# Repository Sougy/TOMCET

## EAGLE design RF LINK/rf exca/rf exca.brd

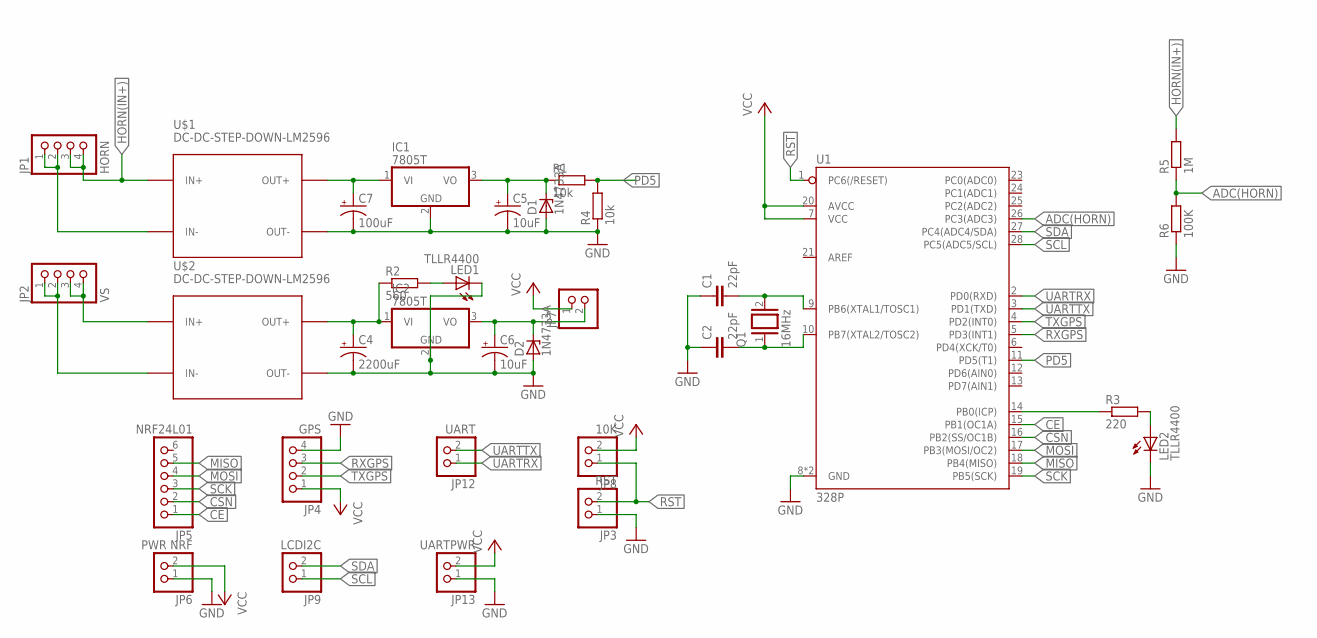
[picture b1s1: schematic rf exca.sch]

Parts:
C1, C2: 22pF; C025-024X044
C4: 2200uF; E5-13
C5, C6: 10uF; E2,5-6E
C7: 100uF; E2,5-7
D1, D2: 1N4733A; DO41Z10
IC1, IC2: 7805T; TO220H
JP1: HORN; 1X04
JP2: VS; 1X04
JP3: RST; 1X02
JP4: GPS; 1X04
JP5: NRF24L01; 1X06
JP6: PWR NRF; 1X02
JP7: PINHD-1X2; 1X02
JP8: 10K; 1X02
JP9: LCDI2C; 1X02
JP12: UART; 1X02
JP13: UARTPWR; 1X02
LED1, LED2: TLLR4400; LED3MM
Q1: 16MHz; QS
R1, R4: 10k; 0207/12
R2: 560; 0207/12
R3: 220; 0207/12
R5: 1M; 0207/12
R6: 100K; 0207/12
U1: 328P; DIP28
U$1, U$2: DC-DC-STEP-DOWN-LM2596

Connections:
ADC(HORN): R5.1, R6.2, U1.26 (PC3(ADC3))
CE: JP5.1, U1.15 (PB1(OC1A))
CSN: JP5.2, U1.16 (PB2(SS/OC1B))
GND: C1.1, C2.1, C4.-, C5.-, C6.-, C7.-, D1.A, D2.A, IC1.2 (GND), IC2.2 (GND), JP3.1, JP4.4, JP6.1, JP13.1, LED1.K (C), LED2.K (C), R4.1, R6.1, U1.8 (GND), U1.22 (GND), U$1.OUT-, U$2.OUT-
HORN(IN+): JP1.3, JP1.4, R5.2, U$1.IN+
MISO: JP5.5, U1.18 (PB4(MISO))
MOSI: JP5.4, U1.17 (PB3(MOSI/OC2))
unnamed: C1.2, Q1.2, U1.9 (PB6(XTAL1/TOSC1))
unnamed: C2.2, Q1.1, U1.10 (PB7(XTAL2/TOSC2))
unnamed: JP1.1, JP1.2, U$1.IN-
unnamed: JP2.3, JP2.4, U$2.IN+
unnamed: JP2.1, JP2.2, U$2.IN-
unnamed: LED2.A, R3.2
unnamed: LED1.A, R2.2
unnamed: C7.+, IC1.1 (VI), U$1.OUT+
unnamed: C6.+, D2.C, IC2.3 (VO), JP7.2
unnamed: C5.+, D1.C, IC1.3 (VO), R1.1
unnamed: R3.1, U1.14 (PB0(ICP))
unnamed: C4.+, IC2.1 (VI), R2.1, U$2.OUT+
PD5: R1.2, R4.2, U1.11 (PD5(T1))
RST: JP3.2, JP8.1, U1.1 (PC6(/RESET))
RXGPS: JP4.3, U1.5 (PD3(INT1))
SCK: JP5.3, U1.19 (PB5(SCK))
SCL: JP9.1, U1.28 (PC5(ADC5/SCL))
SDA: JP9.2, U1.27 (PC4(ADC4/SDA))
TXGPS: JP4.2, U1.4 (PD2(INT0))
UARTRX: JP12.1, U1.2 (PD0(RXD))
UARTTX: JP12.2, U1.3 (PD1(TXD))
VCC: JP4.1, JP6.2, JP7.1, JP8.2, JP13.2, U1.7 (VCC), U1.20 (AVCC)

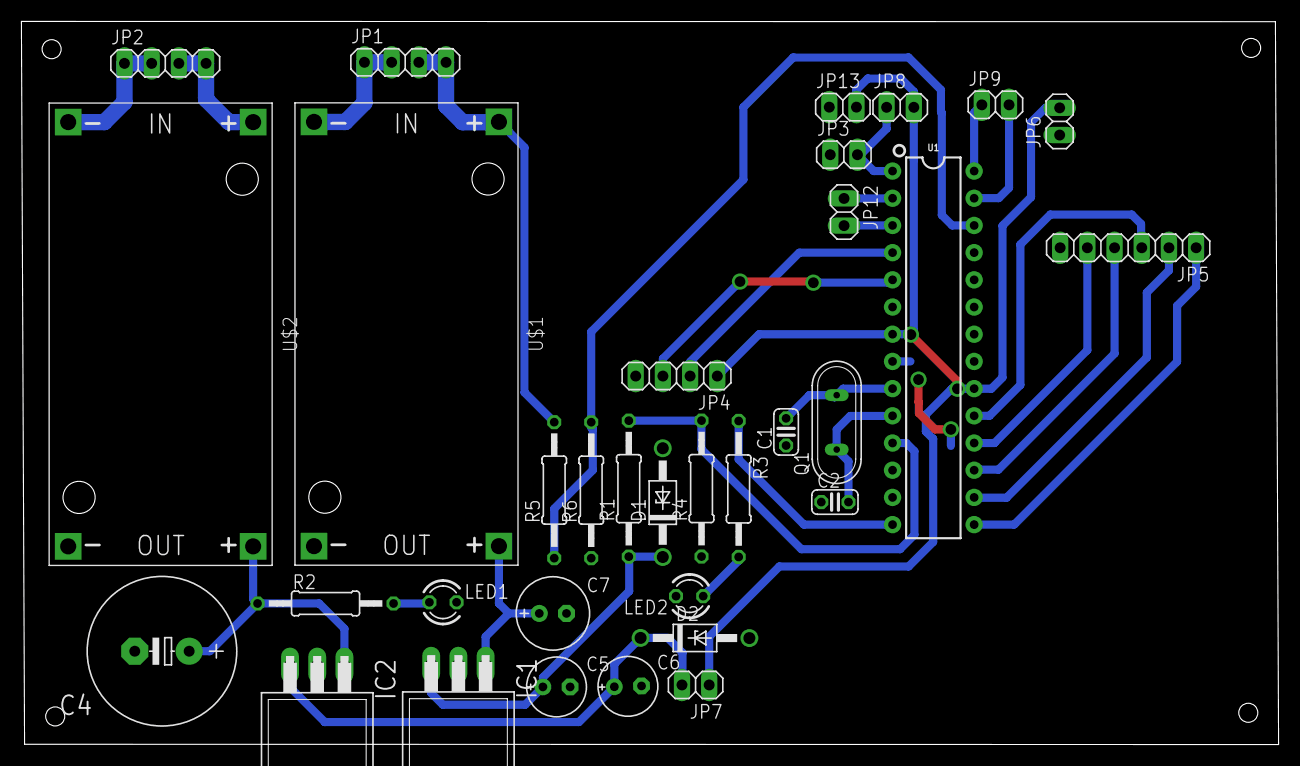
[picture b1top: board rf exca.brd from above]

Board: 2 copper layers, 117.4 x 67.5 mm, 33 parts (0 on the bottom side), 29 nets.

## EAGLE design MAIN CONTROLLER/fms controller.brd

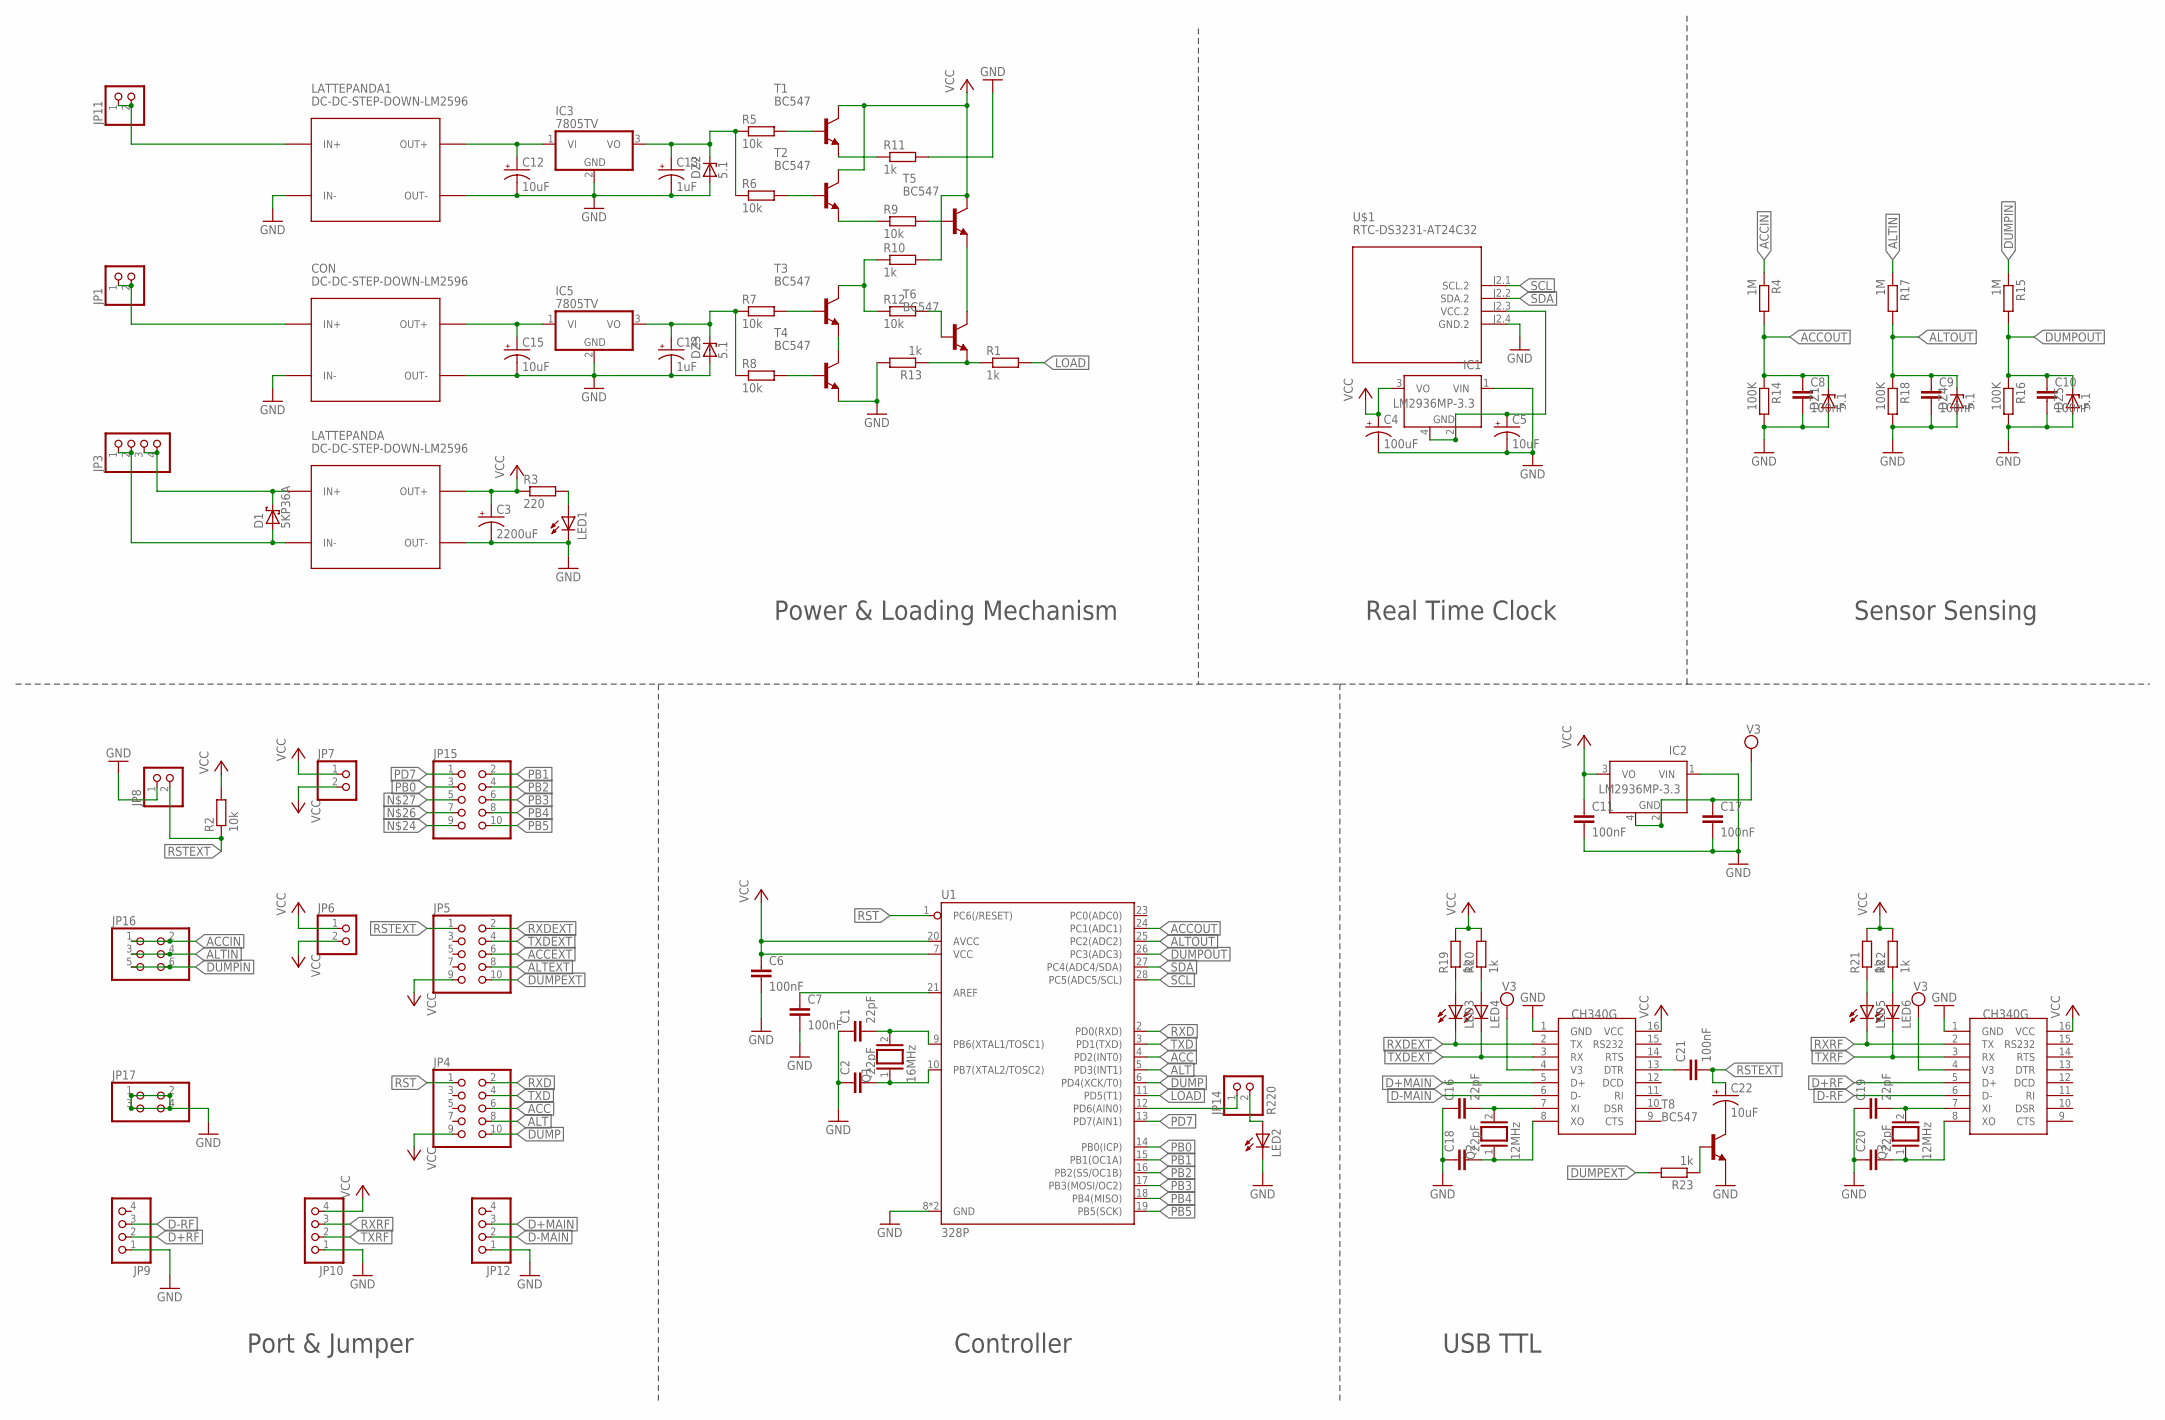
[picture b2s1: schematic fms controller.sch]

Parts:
C1, C2, C16, C18, C19, C20: 22pF; C2.5-3
C3: 2200uF; E5-13
C4: 100uF; E2-5
C5, C12, C15, C22: 10uF; E2-5
C6, C7, C8, C9, C10, C11, C17, C21: 100nF; C025-040X050
C13, C14: 1uF; E2-5
CON: DC-DC-STEP-DOWN-LM2596
D1: 5KP36A; P6T15
DZ1, DZ2, DZ3, DZ4, DZ5: 5.1; DO35Z10
IC1, IC2: LM2936MP-3.3; SOT223
IC3, IC5: 7805TV; TO220V
JP1, JP6, JP7, JP8, JP11: PINHD-1X2; 1X02
JP3, JP9, JP10, JP12: PINHD-1X4; 1X04
JP4, JP5, JP15: PINHD-2X5; 2X05
JP14: R220; 1X02
JP16: PINHD-2X3; 2X03
JP17: PINHD-2X2; 2X02
LATTEPANDA, LATTEPANDA1: DC-DC-STEP-DOWN-LM2596
LED1, LED2, LED3, LED4, LED5, LED6: LED3MM
Q1: 16MHz; QS
Q2, Q3: 12MHz; QS
R1, R10, R11, R13, R19, R20, R21, R22, R23: 1k; 0309/10
R2, R5, R6, R7, R8, R9, R12: 10k; 0309/10
R3: 220; 0309/10
R4, R15, R17: 1M; 0309/10
R14, R16, R18: 100K; 0309/10
T1, T2, T3, T4, T5, T6, T8: BC547; TO92
U1: 328P; DIP28
U$1: RTC-DS3231-AT24C32
U$2, U$3: CH340G; SOIC16

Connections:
ACC: JP4.6, U1.4 (PD2(INT0))
ACCEXT: JP5.6
ACCIN: JP16.1, JP16.2, R4.1
ACCOUT: C8.1, DZ1.C, R4.2, R14.1, U1.24 (PC1(ADC1))
ALT: JP4.8, U1.5 (PD3(INT1))
ALTEXT: JP5.8
ALTIN: JP16.3, JP16.4, R17.1
ALTOUT: C9.1, DZ4.C, R17.2, R18.1, U1.25 (PC2(ADC2))
D+MAIN: JP12.3, U$2.5 (D+)
D+RF: JP9.2, U$3.5 (D+)
D-MAIN: JP12.2, U$2.6 (D-)
D-RF: JP9.3, U$3.6 (D-)
DUMP: JP4.10, U1.6 (PD4(XCK/T0))
DUMPEXT: JP5.10, R23.2
DUMPIN: JP16.5, JP16.6, R15.1
DUMPOUT: C10.1, DZ5.C, R15.2, R16.1, U1.26 (PC3(ADC3))
GND: C1.1, C2.1, C3.-, C4.-, C5.-, C6.2, C7.2, C8.2, C9.2, C10.2, C11.2, C12.-, C13.-, C14.-, C15.-, C16.1, C17.2, C18.1, C19.1, C20.1, CON.IN-, CON.OUT-, DZ1.A, DZ2.A, DZ3.A, DZ4.A, DZ5.A, IC1.1 (VIN), IC2.1 (VIN), IC3.2 (GND), IC5.2 (GND), JP8.1, JP9.1, JP10.1, JP12.1, JP17.1, JP17.2, JP17.3, JP17.4, LATTEPANDA.OUT-, LATTEPANDA1.IN-, LATTEPANDA1.OUT-, LED1.K (C), LED2.K (C), R11.2, R13.2, R14.2, R16.2, R18.2, T4.1 (E), T8.1 (E), U1.8 (GND), U1.22 (GND), U$1.J2.4 (GND.2), U$2.1 (GND), U$3.1 (GND)
LOAD: R1.2, U1.11 (PD5(T1))
unnamed: JP11.1, JP11.2, LATTEPANDA1.IN+
unnamed: CON.IN+, JP1.1, JP1.2
unnamed: LED1.A, R3.2
unnamed: D1.A, JP3.1, JP3.2, LATTEPANDA.IN-
unnamed: D1.C, JP3.3, JP3.4, LATTEPANDA.IN+
unnamed: C12.+, IC3.1 (VI), LATTEPANDA1.OUT+
unnamed: C1.2, Q1.2, U1.9 (PB6(XTAL1/TOSC1))
unnamed: JP14.1, U1.12 (PD6(AIN0))
unnamed: C13.+, DZ2.C, IC3.3 (VO), R5.1, R6.1
unnamed: R1.1, R13.1, T6.1 (E)
unnamed: C15.+, CON.OUT+, IC5.1 (VI)
unnamed: C2.2, Q1.1, U1.10 (PB7(XTAL2/TOSC2))
unnamed: C14.+, DZ3.C, IC5.3 (VO), R7.1, R8.1
unnamed: JP14.2, LED2.A
unnamed: C5.+, IC1.2 (GND), IC1.4 (GND), U$1.J2.3 (VCC.2)
unnamed: C7.1, U1.21 (AREF)
unnamed: C19.2, Q3.2, U$3.7 (XI)
unnamed: R11.1, T1.1 (E)
unnamed: C20.2, Q3.1, U$3.8 (XO)
unnamed: C16.2, Q2.2, U$2.7 (XI)
unnamed: R5.2, T1.2 (B)
unnamed: C18.2, Q2.1, U$2.8 (XO)
unnamed: R10.1, R12.1, T3.3 (C)
unnamed: R6.2, T2.2 (B)
unnamed: C21.1, U$2.13 (DTR)
unnamed: R7.2, T3.2 (B)
unnamed: C22.-, T8.3 (C)
unnamed: R9.1, T2.1 (E)
unnamed: R9.2, T5.2 (B)
unnamed: R8.2, T4.2 (B)
unnamed: LED4.A, R20.1
unnamed: T3.1 (E), T4.3 (C)
unnamed: LED3.A, R19.1
unnamed: R12.2, T6.2 (B)
unnamed: T5.1 (E), T6.3 (C)
unnamed: LED5.A, R21.1
unnamed: LED6.A, R22.1
unnamed: R23.1, T8.2 (B)
PB0: JP15.3, U1.14 (PB0(ICP))
PB1: JP15.2, U1.15 (PB1(OC1A))
PB2: JP15.4, U1.16 (PB2(SS/OC1B))
PB3: JP15.6, U1.17 (PB3(MOSI/OC2))
PB4: JP15.8, U1.18 (PB4(MISO))
PB5: JP15.10, U1.19 (PB5(SCK))
PD7: JP15.1, U1.13 (PD7(AIN1))
RST: JP4.1, U1.1 (PC6(/RESET))
RSTEXT: C21.2, C22.+, JP5.1, JP8.2, R2.1
RXD: JP4.2, U1.2 (PD0(RXD))
RXDEXT: JP5.2, LED3.K (C), U$2.2 (TX)
RXRF: JP10.3, LED5.K (C), U$3.2 (TX)
SCL: U1.28 (PC5(ADC5/SCL)), U$1.J2.1 (SCL.2)
SDA: U1.27 (PC4(ADC4/SDA)), U$1.J2.2 (SDA.2)
TXD: JP4.4, U1.3 (PD1(TXD))
TXDEXT: JP5.4, LED4.K (C), U$2.3 (RX)
TXRF: JP10.2, LED6.K (C), U$3.3 (RX)
VCC: C3.+, C4.+, C6.1, C11.1, IC1.3 (VO), IC2.3 (VO), JP4.9, JP5.9, JP6.1, JP6.2, JP7.1, JP7.2, JP10.4, LATTEPANDA.OUT+, R2.2, R3.1, R10.2, R19.2, R20.2, R21.2, R22.2, T1.3 (C), T2.3 (C), T5.3 (C), U1.7 (VCC), U1.20 (AVCC), U$2.16 (VCC), U$3.16 (VCC)
VSS: C17.1, IC2.2 (GND), IC2.4 (GND), U$2.4 (V3), U$3.4 (V3)

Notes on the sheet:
Power & Loading Mechanism
Real Time Clock
Sensor Sensing
Port & Jumper
Controller
USB TTL

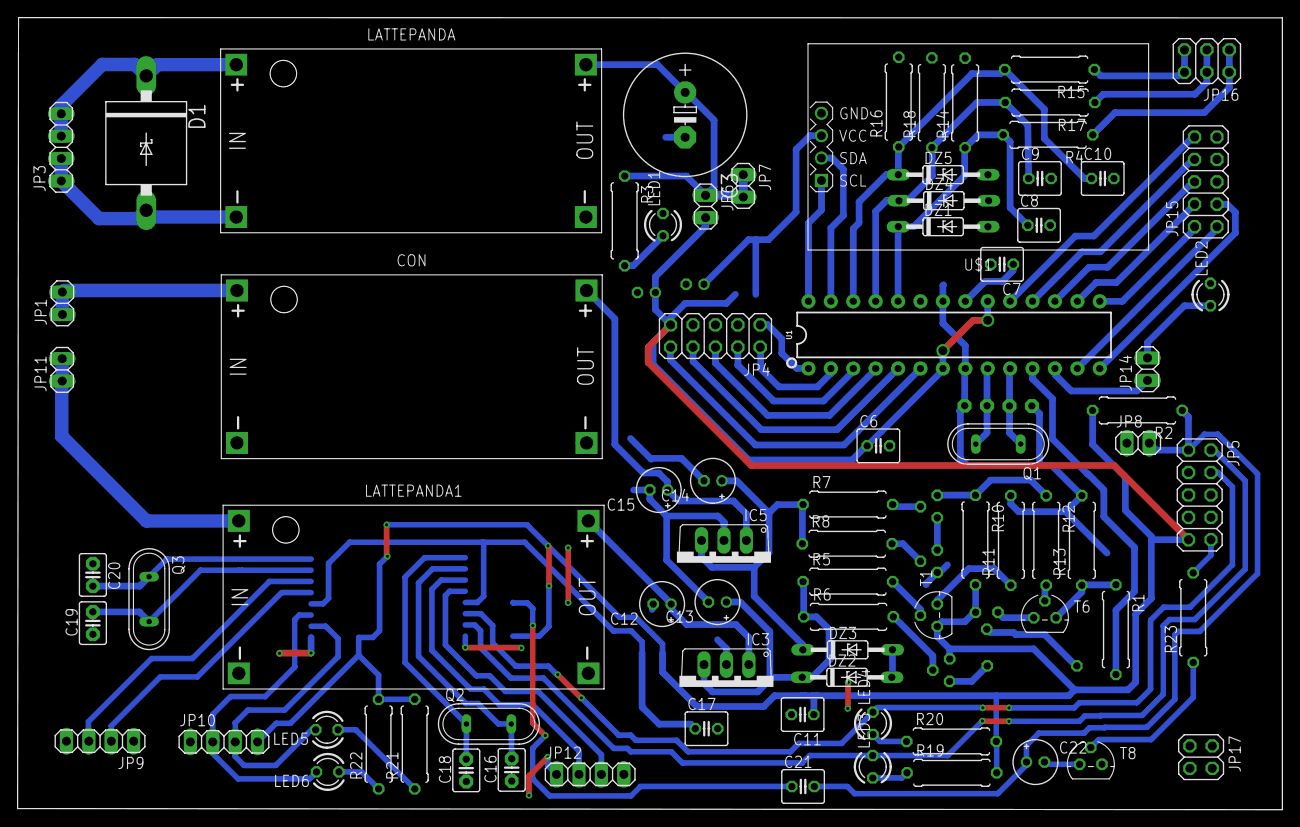
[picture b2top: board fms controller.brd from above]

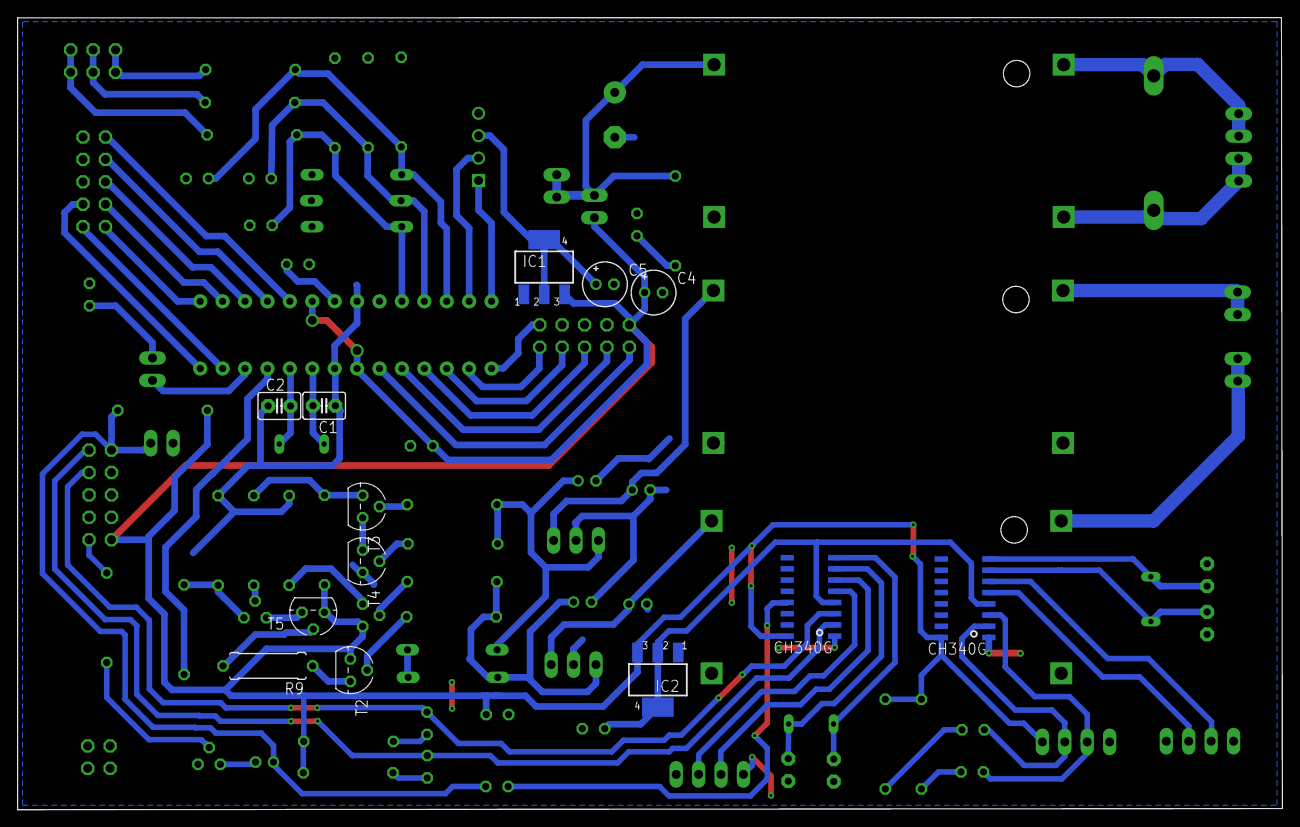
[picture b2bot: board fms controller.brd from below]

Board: 2 copper layers, 143.3 x 89.8 mm, 93 parts (13 on the bottom side), 73 nets.

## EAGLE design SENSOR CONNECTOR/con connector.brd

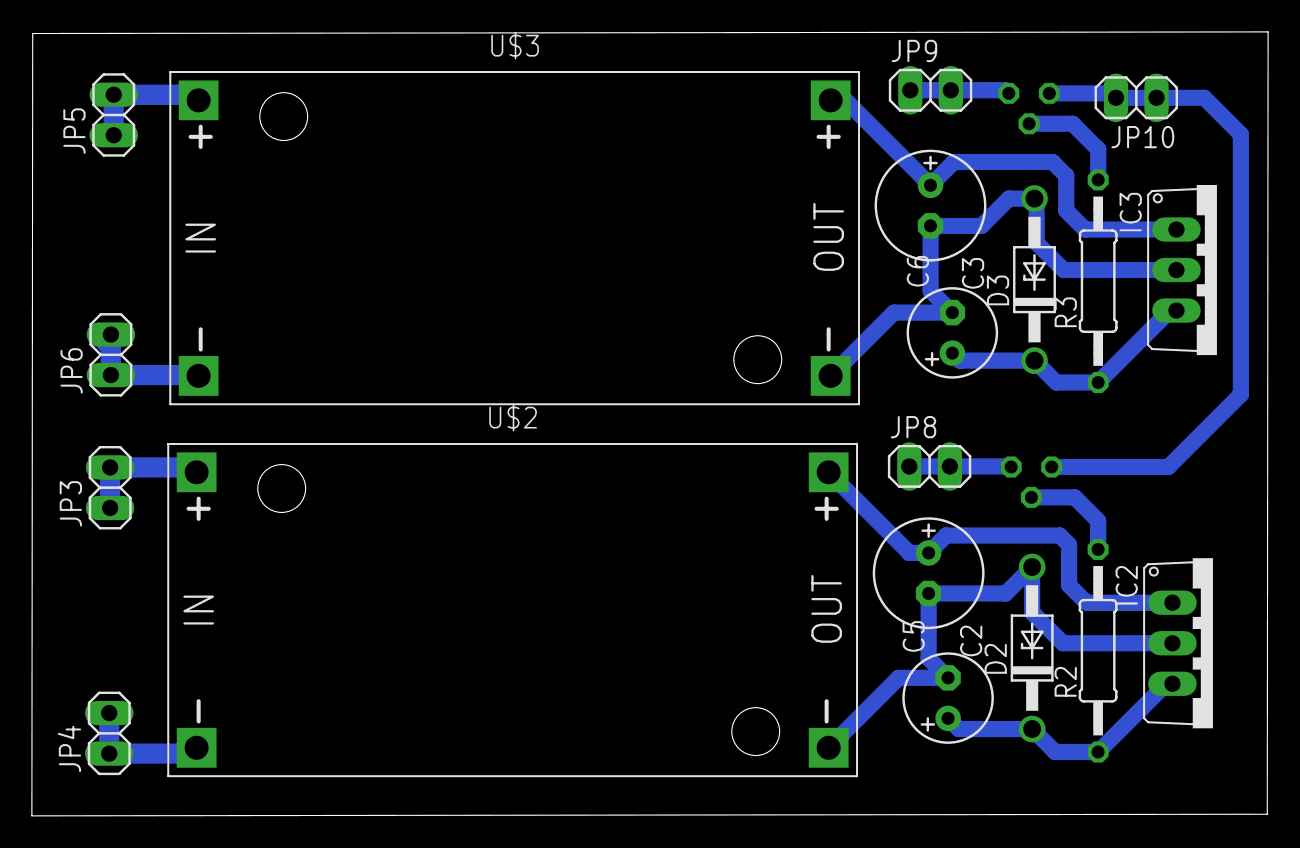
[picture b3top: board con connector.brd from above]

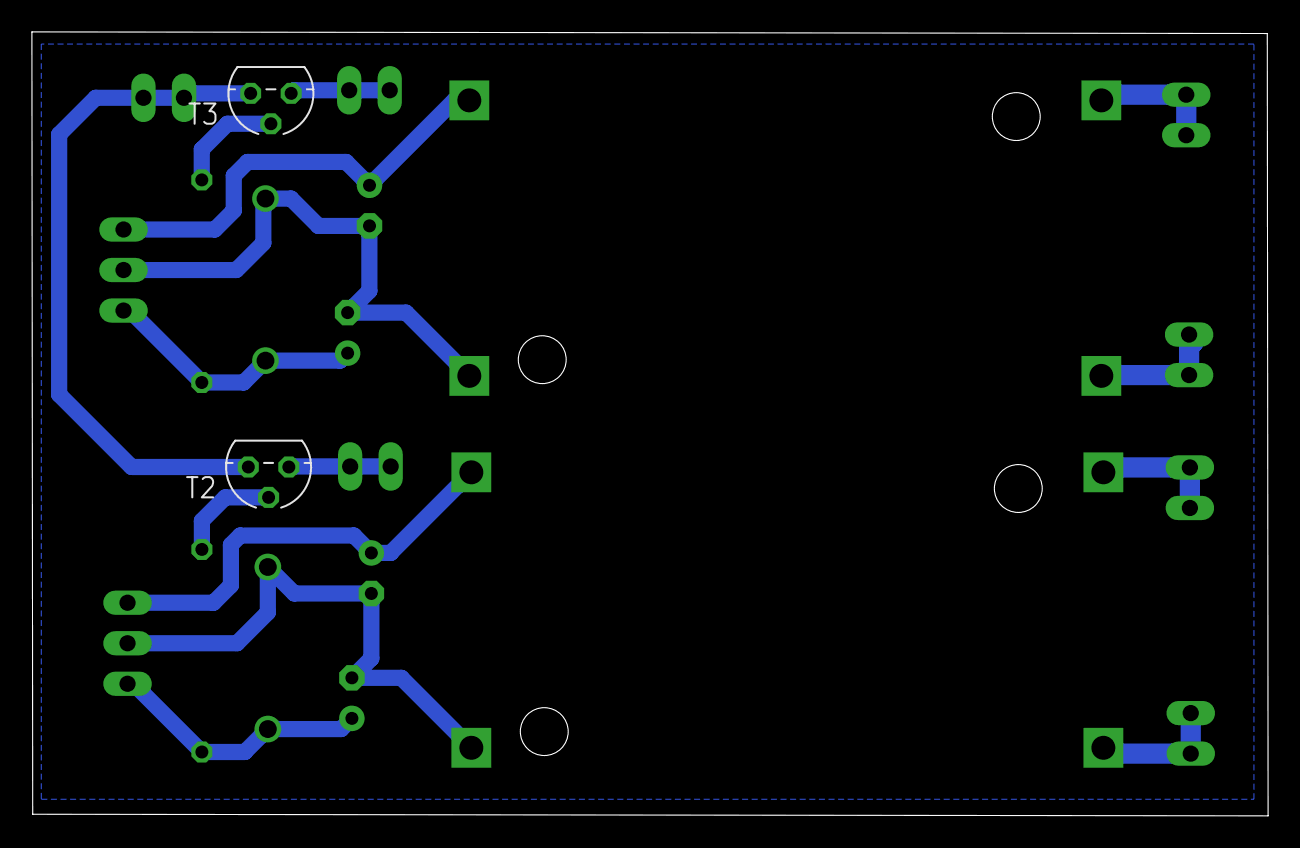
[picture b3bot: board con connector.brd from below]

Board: 2 copper layers, 77.5 x 49.1 mm, 21 parts (2 on the bottom side), 14 nets.

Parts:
C2: 100uF; E2,5-7
C3: 100uF'; E2,5-7
C5, C6: 10uF; E2,5-6
D2, D3: 1N4733A; DO41Z10
IC2, IC3: 7805TV; TO220V
JP3, JP4, JP5, JP6, JP8, JP9: 1X02
JP10: GND; 1X02
R2, R3: 10k; 0207/12
T2, T3: BC547; TO92
U$2, U$3: DC-DC-STEP-DOWN-LM2596

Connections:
GND: C2.-, C3.-, C5.-, C6.-, D2.A, D3.A, IC2.2, IC3.2, U$2.OUT-, U$3.OUT-
unnamed: C2.+, IC2.1, U$2.OUT+
unnamed: C3.+, IC3.1, U$3.OUT+
unnamed: C5.+, D2.C, IC2.3, R2.1
unnamed: C6.+, D3.C, IC3.3, R3.1
unnamed: R2.2, T2.2
unnamed: R3.2, T3.2
unnamed: JP10.1, JP10.2, T2.1, T3.1
unnamed: JP3.1, JP3.2, U$2.IN+
unnamed: JP4.1, JP4.2, U$2.IN-
unnamed: JP5.1, JP5.2, U$3.IN+
unnamed: JP6.1, JP6.2, U$3.IN-
unnamed: JP8.1, JP8.2, T2.3
unnamed: JP9.1, JP9.2, T3.3

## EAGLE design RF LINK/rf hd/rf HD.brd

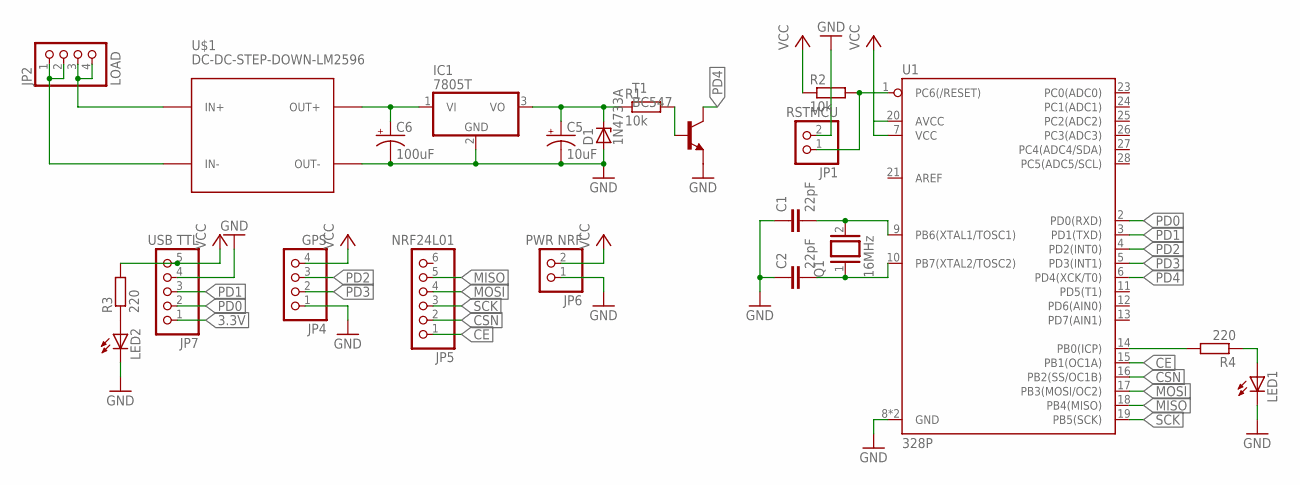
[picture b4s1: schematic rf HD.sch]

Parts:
C1, C2: 22pF; C025-024X044
C5: 10uF; E2,5-6E
C6: 100uF; E2,5-7
D1: 1N4733A; DO41Z10
IC1: 7805T; TO220H
JP1: RSTMCU; 1X02
JP2: LOAD; 1X04
JP4: GPS; 1X04
JP5: NRF24L01; 1X06
JP6: PWR NRF; 1X02
JP7: USB TTL; 1X05
LED1, LED2: LED3MM
Q1: 16MHz; QS
R1, R2: 10k; 0207/12
R3, R4: 220; 0207/12
T1: BC547; TO92
U1: 328P; DIP28
U$1: DC-DC-STEP-DOWN-LM2596

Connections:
3.3V: JP7.1
CE: JP5.1, U1.15 (PB1(OC1A))
CSN: JP5.2, U1.16 (PB2(SS/OC1B))
GND: C1.1, C2.1, C5.-, C6.-, D1.A, IC1.2 (GND), JP1.2, JP4.1, JP6.1, JP7.4, LED1.K (C), LED2.K (C), T1.1 (E), U1.8 (GND), U1.22 (GND), U$1.OUT-
MISO: JP5.5, U1.18 (PB4(MISO))
MOSI: JP5.4, U1.17 (PB3(MOSI/OC2))
unnamed: C1.2, Q1.2, U1.9 (PB6(XTAL1/TOSC1))
unnamed: C2.2, Q1.1, U1.10 (PB7(XTAL2/TOSC2))
unnamed: R1.2, T1.2 (B)
unnamed: JP1.1, R2.2, U1.1 (PC6(/RESET))
unnamed: JP2.3, JP2.4, U$1.IN+
unnamed: C5.+, D1.C, IC1.3 (VO), R1.1
unnamed: LED2.A, R3.1
unnamed: LED1.A, R4.1
unnamed: JP2.1, JP2.2, U$1.IN-
unnamed: C6.+, IC1.1 (VI), U$1.OUT+
PB0: R4.2, U1.14 (PB0(ICP))
PD0: JP7.2, U1.2 (PD0(RXD))
PD1: JP7.3, U1.3 (PD1(TXD))
PD2: JP4.3, U1.4 (PD2(INT0))
PD3: JP4.2, U1.5 (PD3(INT1))
PD4: T1.3 (C), U1.6 (PD4(XCK/T0))
SCK: JP5.3, U1.19 (PB5(SCK))
VCC: JP4.4, JP6.2, JP7.5, R2.1, R3.2, U1.7 (VCC), U1.20 (AVCC)

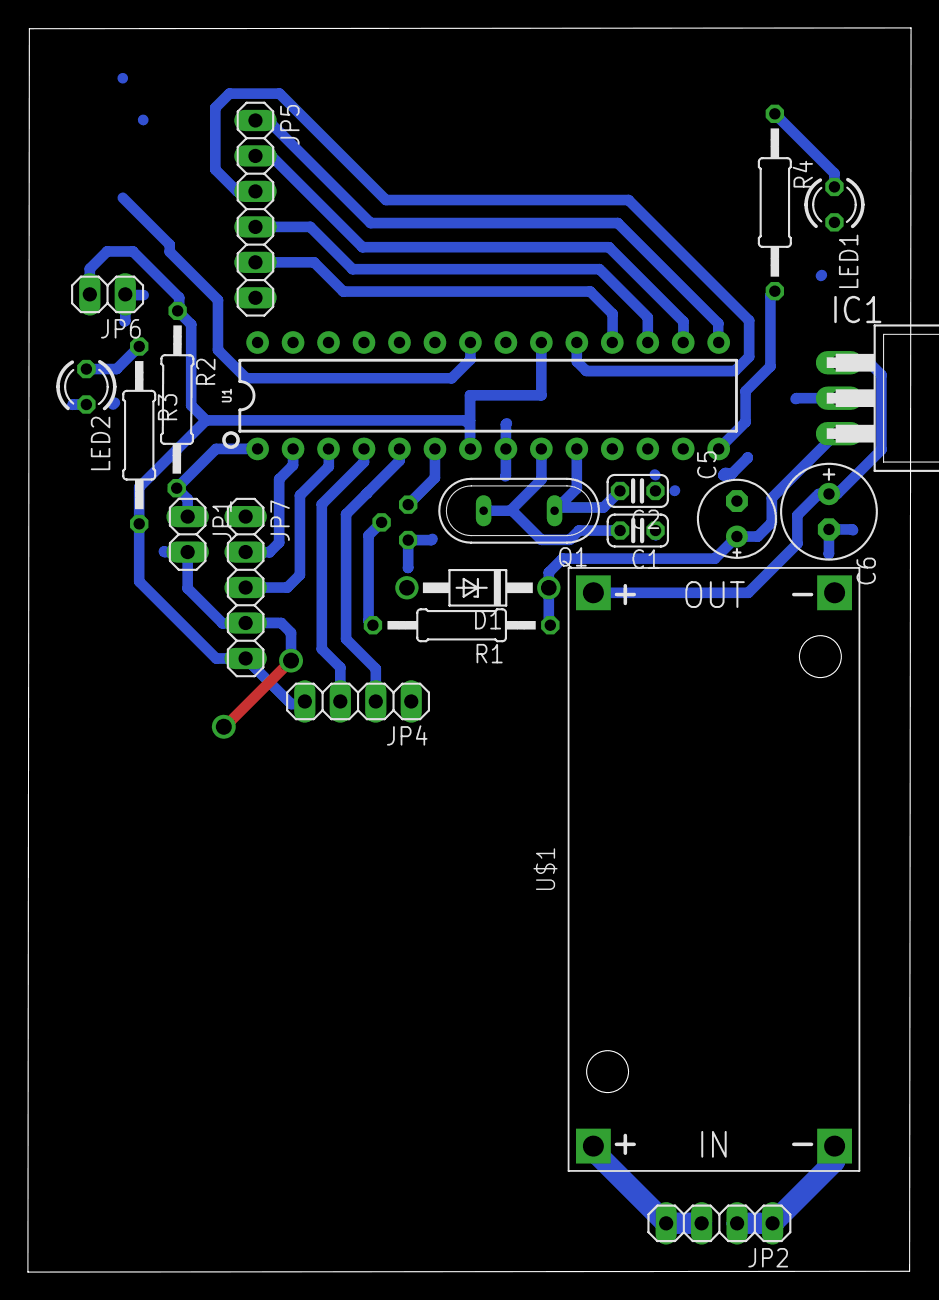
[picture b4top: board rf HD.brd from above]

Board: 2 copper layers, 63.2 x 89.1 mm, 22 parts (1 on the bottom side), 23 nets.

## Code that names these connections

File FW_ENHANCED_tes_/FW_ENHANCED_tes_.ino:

#include <Wire.h>
#include "RTClib.h"

#define HOURDIV 3600
#define MINDIV 60
#define AT24C32 0x57
//tes
DateTime now;
RTC_DS3231 rtc;

//Engine status & Sensor status
String ENGSTAT, TRIGSTAT;
unsigned long PREVSEN = 0;
unsigned long PREVSET = 0;
unsigned long PREVTES = 0;

typedef struct
{
  String DATAIN;
  String SETDATA[12];
  bool INHM   = false;
  bool START  = false;
  bool END    = false;
  uint8_t VAL = 0;
  uint8_t SEQ = 0;
  uint8_t I;
  char INBYTE;
  char MSG[20];
  byte IDX;
} SERCOM; SERCOM VARSER;

typedef struct
{
  String CURTIME;
  String CURDATE;
  uint8_t SEC;
  uint8_t MIN;
  uint8_t SEQ;
  uint32_t HR;
  char RCVDATA[12];
  char DATA2WRT[12];
  unsigned long SVDHM;
  unsigned long LASTUNIX;
  unsigned long DELTATIME;
  unsigned long ELAPSED;
  bool LTCHM = false;

} RTCOM; RTCOM VARRTC;

void setup() {
  // put your setup code here, to run once:
  DDRD &= ~(1 << PIND3); //ACC
  DDRD &= ~(1 << PIND4); //DUMP
  DDRD &= ~(1 << PIND7); //ALT
  DDRD  |= (1 << PIND6);
  PORTD |= (1 << PIND3);
  PORTD |= (1 << PIND4);
  PORTD |= (1 << PIND7);
  Wire.begin();
  rtc.begin();
  Serial.begin(9600);
  RDHMRTC();
  
}

void loop() {
  // put your main code here, to run repeatedly:
  LTCSEN();
  PROG();
}

void SERFLUSH(void)
{
  while (true)
  {
    delay(10);
    if (Serial.available())
    {
      while (Serial.available())
        Serial.read();
      continue;
    }
    else
      break;
  }
}

void LTCSER()
{
  while (Serial.available() > 0)
  {
    VARSER.INBYTE = Serial.read();
    if (VARSER.INBYTE == '<')
    {
      VARSER.START     = true;
      VARSER.IDX       = 0;
      VARSER.MSG[VARSER.IDX]  = '\0';
    }
    else if (VARSER.INBYTE == '>')
    {
      VARSER.END = true;
      break;
    }
    else
    {
      if (VARSER.IDX < 20)
      {
        VARSER.MSG[VARSER.IDX] = VARSER.INBYTE;
        VARSER.IDX++;
        VARSER.MSG[VARSER.IDX] = '\0';
      }
    }
  }

  if (VARSER.START && VARSER.END)
  {
    VARSER.VAL              = atoi(VARSER.MSG);
    Serial.println(String("VAL: ") + VARSER.VAL);
    VARSER.IDX              = 0;
    VARSER.MSG[VARSER.IDX]  = '\0';
    VARSER.START            = false;
    VARSER.END              = false;
  }
}

void PARSETHM()
{
  while (Serial.available() > 0) {
    char INCHAR = (char)Serial.read();
    VARSER.DATAIN += INCHAR;
    if (INCHAR == '\n') {
      VARSER.INHM  = true;
    }
  }
  if (VARSER.INHM) {
    for (VARSER.I = 1; VARSER.I < VARSER.DATAIN.length(); VARSER.I++) {
      if (VARSER.DATAIN[VARSER.I] == '<') {
        VARSER.SETDATA[VARSER.SEQ] = "";
      }
      else if (VARSER.DATAIN[VARSER.I] == '>') {
        VARSER.SEQ++;
        VARSER.SETDATA[VARSER.SEQ] = "";
      }
      else {
        VARSER.SETDATA[VARSER.SEQ] = VARSER.SETDATA[VARSER.SEQ] + VARSER.DATAIN[VARSER.I];
      }
    }
    //B4 flushing(SETDATA[0]) need to be saved to rtc saving var
    VARRTC.SVDHM          = 0;
    VARRTC.SVDHM          = VARSER.SETDATA[0].toInt();
    Serial.println(String("SVDHM: ") + VARRTC.SVDHM);
    HMWRT(VARRTC.SVDHM);
    VARSER.SEQ            = 0;
    VARSER.SETDATA[0]     = "";
    VARSER.DATAIN         = "";
  }
}

void LTCSEN()
{
  HMS();
  uint8_t PIN3ACC, PIN4DUMP, PIN7ALT;
  PIN3ACC   = digitalRead(3);
  PIN4DUMP  = digitalRead(4);
  PIN7ALT   = digitalRead(7);


  if (millis() - PREVSEN >= 1000) {
    Serial.println(String("PIN3ACC: ") + PIN3ACC);
    Serial.println(String("PIN4DUMP: ") + PIN4DUMP);
    Serial.println(String("PIN7ALT: ") + PIN7ALT);

    if ((!(PIND & (1 << PIND3))) && (PIND & (1 << PIND7)) && (PIND & (1 << PIND4)))
    {
      ENGSTAT   = "IN";
      TRIGSTAT  = "";
      Serial.print(String(VARRTC.CURDATE) + "|" + VARRTC.CURTIME + "|" + VARRTC.HR + "|" +
                   VARRTC.MIN + "|" + VARRTC.SEC + "|" + ENGSTAT + "|" + TRIGSTAT + "|");
    }
    else if ((!(PIND & (1 << PIND3))) && (!(PIND & (1 << PIND7))) && (PIND & (1 << PIND4)))
    {
      ENGSTAT = "RG";
      TRIGSTAT  = "";
      Serial.print(String(VARRTC.CURDATE) + "|" + VARRTC.CURTIME + "|" + VARRTC.HR + "|" +
                   VARRTC.MIN + "|" + VARRTC.SEC + "|" + ENGSTAT + "|" + TRIGSTAT + "|");
    }
    else if ((!(PIND & (1 << PIND3))) && (!(PIND & (1 << PIND7))) && (!(PIND & (1 << PIND4))))
    {
      ENGSTAT = "RG";
      TRIGSTAT = "DG";
      Serial.print(String(VARRTC.CURDATE) + "|" + VARRTC.CURTIME + "|" + VARRTC.HR + "|" +
                   VARRTC.MIN + "|" + VARRTC.SEC + "|" + ENGSTAT + "|" + TRIGSTAT + "|");
    }
    else {
      ENGSTAT = "IF";
      TRIGSTAT = "";
      Serial.print(String(VARRTC.CURDATE) + "|" + VARRTC.CURTIME + "|" + VARRTC.HR + "|" +
                   VARRTC.MIN + "|" + VARRTC.SEC + "|" + ENGSTAT + "|" + TRIGSTAT + "|");
    }
    PREVSEN = millis();
    Serial.println();
  }
}

void WRTBYTE(int DVCADDR, unsigned int EEADDR, byte DATA)
{
  int RDATA = DATA;
  Wire.beginTransmission(DVCADDR);
  Wire.write((int)(EEADDR >> 8));
  Wire.write((int)(EEADDR & 0xFF));
  Wire.write(RDATA);
  Wire.endTransmission();
}

void WRTPAGE(int DVCADDR, unsigned int EEADDR, byte* DATA, byte LENGTH)
{
  Wire.beginTransmission(DVCADDR);
  Wire.write((int)(EEADDR >> 8));
  Wire.write((int)(EEADDR & 0xFF));
  byte DATASEQ;
  for (DATASEQ = 0; DATASEQ < LENGTH; DATASEQ++) {
    Wire.write(DATA[DATASEQ]);
    Wire.endTransmission();
  }
}

byte RDBYTE(int DVCADDR, unsigned int EEADDR)
{
  byte RDATA  = 0xFF;
  Wire.beginTransmission(DVCADDR);
  Wire.write((int)(EEADDR >> 8));
  Wire.write((int)(EEADDR & 0xFF));
  Wire.endTransmission();
  Wire.requestFrom(DVCADDR, 1);
  if (Wire.available()) RDATA = Wire.read();
  return RDATA;
}

void RDBUF(int DVCADDR, unsigned int EEADDR, byte *BUFFER, int LENGTH)
{
  Wire.beginTransmission(DVCADDR);
  Wire.write((int)(EEADDR >> 8));
  Wire.write((int)(EEADDR & 0xFF));
  Wire.endTransmission();
  Wire.requestFrom(DVCADDR, LENGTH);
  int DATASEQ = 0;
  for (DATASEQ = 0; DATASEQ < LENGTH; DATASEQ++)
    if (Wire.available()) BUFFER[DATASEQ] = Wire.read();
}

void HMS()
{
  now = rtc.now();

  if ((!(PIND & (1 << PIND3))) && (!(PIND & (1 << PIND7)))) {
    if (!VARRTC.LTCHM) {
      RDHMRTC();
      VARRTC.ELAPSED += VARRTC.DELTATIME;
      VARRTC.SVDHM += VARRTC.ELAPSED;
      Serial.println(String("SVDHM+DELTATIME: ") + VARRTC.SVDHM);
      VARRTC.LASTUNIX   = 0;
      VARRTC.LASTUNIX   = now.unixtime();
      VARRTC.LTCHM      = true;
    }
    VARRTC.DELTATIME = now.unixtime() - VARRTC.LASTUNIX;
    if(millis() - PREVTES >= 1000){
      Serial.println(String("DELTATIME: ") + VARRTC.DELTATIME);
      PREVTES = millis();
    }
  }
  else {
    VARRTC.LTCHM     = false;
  }
  //saat nyala lg waktunya blm update (SVDHM) //closed need to test NOTE: RESET DELTATIME in 2
  VARRTC.CURTIME  = String(now.hour()) + ":" + now.minute() + ":" + now.second();
  VARRTC.CURDATE  = String(now.year()) + "-" + now.month() + ":" + now.second();
  VARRTC.SEC      = (VARRTC.SVDHM + VARRTC.DELTATIME) % MINDIV;
  VARRTC.MIN      = ((VARRTC.SVDHM + VARRTC.DELTATIME) % HOURDIV) / MINDIV;
  VARRTC.HR       = (VARRTC.SVDHM + VARRTC.DELTATIME) / HOURDIV;
}

void RDHMRTC()
{
  uint8_t ADDR  = 0;
  byte MEMADDR = RDBYTE(AT24C32, 0);

  while (MEMADDR != 0)
  {
    VARRTC.RCVDATA[VARRTC.SEQ] = MEMADDR;
    ADDR++;
    VARRTC.SEQ++;
    MEMADDR = RDBYTE(AT24C32, ADDR);
  }
  VARRTC.SEQ = 0;
  String STRHM(VARRTC.RCVDATA);
  VARRTC.SVDHM = STRHM.toInt();
  Serial.println(String("Read HM RTC: ") + VARRTC.SVDHM);
}

char HMCONV(unsigned long HMVAL)
{
  String STRHM;
  STRHM = String(HMVAL);
  STRHM.toCharArray(VARRTC.DATA2WRT, sizeof(VARRTC.DATA2WRT));
  Serial.println(String("DATA to WRT(char): ") + VARRTC.DATA2WRT);

  return VARRTC.DATA2WRT;
}

void HMWRT(unsigned long DATA2CONV)
{
  HMCONV(DATA2CONV);
  delay(100);
  WRTPAGE(AT24C32, 0, (byte *)VARRTC.DATA2WRT, sizeof(VARRTC.DATA2WRT));
  delay(100);
  Serial.println("DONE SAVE");
}

void PROG()
{
  LTCSER();

  switch (VARSER.VAL) {
    case 3:
      SERFLUSH();
      VARRTC.DELTATIME  = 0;
      VARRTC.ELAPSED    = 0;
      while (!VARSER.INHM) {
        if (millis() - PREVSET >= 1000) {
          Serial.println('#');
          PARSETHM();
          PREVSET = millis();
        }
      }
      Serial.println("DONE SET HM");
      VARSER.INHM = false;
      VARSER.VAL = 0;

      break;

    case 2:
      HMWRT(VARRTC.SVDHM + VARRTC.ELAPSED);
      VARSER.VAL        = 0;
      Serial.println("DONE LOGOUT & SAVE");
      break;
  }
}

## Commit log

2019-10-01 tomcet
    v2
2019-10-02 Update v2
2019-10-02 testing
2019-10-02 UPDATEED 10/2/19/13:55
2019-10-02 UPDATED 10/2/19/15:58
2019-10-02 Rename FW_ENHANCED_tes_.ino to FW_ENHANCED.ino
2019-10-02 UPDATED 2/10/19/14:18
2019-10-02 2/10/19/15:45
2019-10-02 2/10/19/17:04
2019-10-03 3/10/19/10:31
2019-10-03 RELEASED V1
2019-10-03 RELEASED V1.1
2019-10-03 RELEASED V1.2
2019-10-08 FW_HD
2019-10-09 New Updated
2019-10-09 9/10/2019/13:31
2019-10-09 9/10/2019/14:54
2019-10-10 10/10/2019/11:18
2019-10-10 10/10/2019/14:27
2019-10-10 10/10/2019/15:59
2019-10-11 11/10/2019/10:02
2019-10-11 11/10/2019/10:11
2019-10-15 15/10/2019/09:29
2019-10-18 18/10/19/16:02
2019-10-18 18/10/19/16:10
2019-10-23 23/10/19/17:09
2019-10-24 24/10/19/11:22
2019-10-24 24/10/19/11:25
2019-10-24 24/10/19/11:44
2019-10-24 24/10/19/17:05
2019-11-15 15/11/19/16:15
2019-11-16 16/11/19/9:34
2019-11-16 16/11/19/14:26
2019-11-16 16/11/19/14:29
2019-11-16 16/11/19/14:50
2019-11-18 18/11/19/11:34
2019-11-18 18/11/19/14:07
2019-11-18 18/11/19/15:21
2019-11-18 18/11/19/15:26
2019-11-19 19/11/19/08:56
2019-11-19 19/11/19/11:02
2019-11-19 19/11/19/12:01
2019-11-19 19/11/19/12:05
2019-11-19 19/11/19/16:42
2019-11-20 20/11/19/16:17
2019-11-20 20/11/19/16:26
2019-11-21 21/11/19/11:35
2019-11-21 21/11/19/16:05
2019-11-21 21/11/19/16:18
2019-11-27 27/11/19/10:07
2019-12-06 06/12/19/14:04
2019-12-13 13/12/19/10:42
2019-12-13 13/12/19/11:29
2019-12-14 14/12/19/10:10
2019-12-14 14/12/19/14:10
2019-12-17 17/12/19/11:37
2019-12-21 21/12/19/10:46
2019-12-21 21/12/19/11:07
2020-01-02 02/01/2020/08:46
2020-01-04 04/01/2020/08:38
2020-01-08 8/1/20/11:46
2020-01-08 8/1/20/11:53
2020-01-08 8/1/20/14:50
2020-02-03 2/2/2020/8:25
2020-02-07 7/2/2020/9:19
2020-02-10 10/02/2020/09:20
2020-02-20 20/2/2020/10:49
2020-02-28 28/02/2020/10:33
2020-03-06 06/03/2020/14:59
2020-03-09 9/3/2020/14:25

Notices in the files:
parts and their libraries:
diy-modules: Released under the Creative Commons Attribution 4.0 International License: http://creativecommons.org/licenses/by/4.0
SparkFun-IC-Microcontroller: Licensing: Creative Commons ShareAlike 4.0 International - https://creativecommons.org/licenses/by-sa/4.0
